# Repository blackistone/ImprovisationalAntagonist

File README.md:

# ImprovisationalAntagonist
Files from the development of the project merging hostile architectural approaches with machine learning strategies to produce systems that actively oppose performative predictability.
Current revision takes data via OSC from two AD8232 EMG sensonrs via and ESP32, processes that and sound data, and returns a trigger to pass TENS current from and external device when activity is deemed sufficiently predictable.

# Includes
Max files for ingestiona and interpretation of data and sending of shock triggers.  
ESP32 files written for arduino IDE to measure data from two sensors and send/receive OSC.  
KiCAD files for a board assembly allowing a third AD8232 muscle sensor, as well as relay for TENS voltage and indicator LED.

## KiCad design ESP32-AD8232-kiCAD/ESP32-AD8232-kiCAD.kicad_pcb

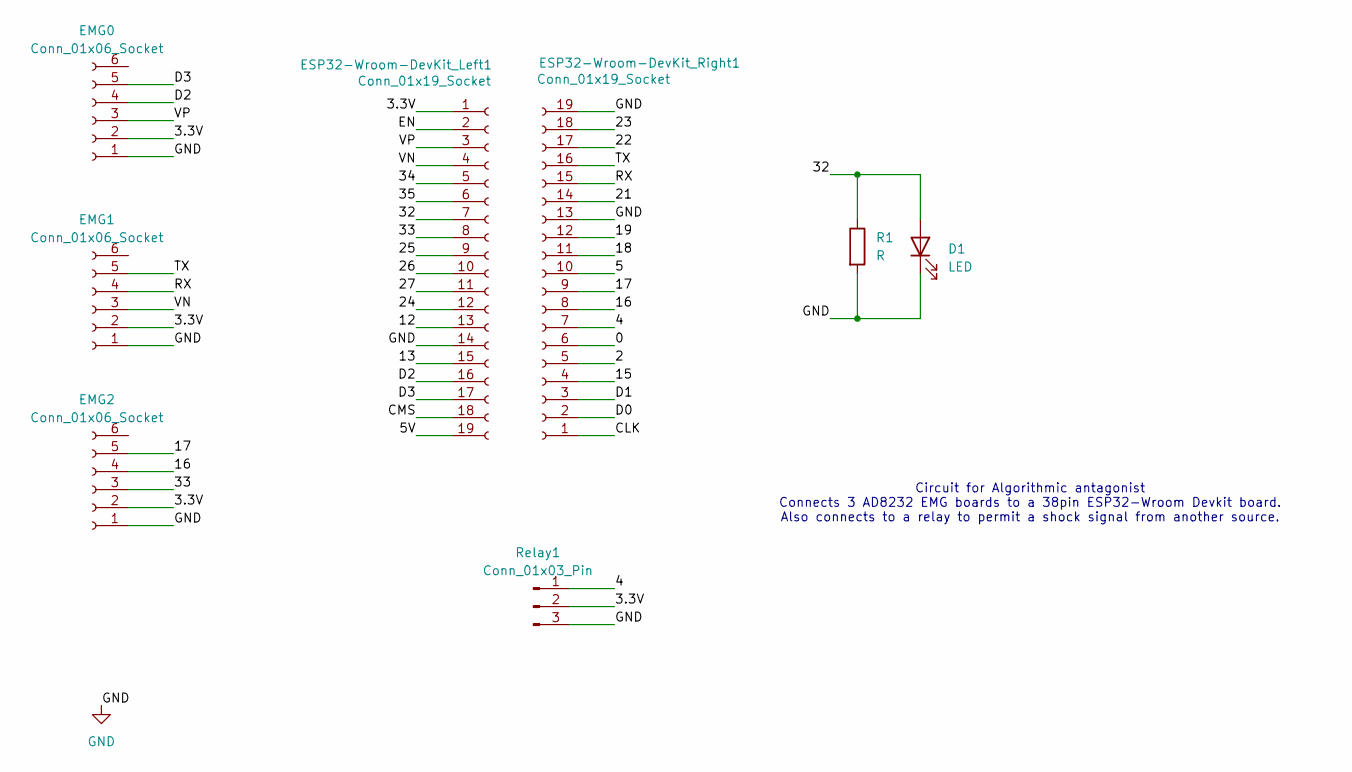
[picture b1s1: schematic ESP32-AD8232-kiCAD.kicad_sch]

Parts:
D1: LED; LED_D5.0mm
EMG0, EMG1, EMG2: Conn_01x06_Socket; PinSocket_1x06_P2.54mm_Vertical
ESP32-Wroom-DevKit_Left1, ESP32-Wroom-DevKit_Right1: Conn_01x19_Socket; PinSocket_1x19_P2.54mm_Vertical
R1: R; R_Axial_DIN0207_L6.3mm_D2.5mm_P15.24mm_Horizontal
Relay1: Conn_01x03_Pin; PinSocket_1x03_P2.54mm_Horizontal

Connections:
/0: ESP32-Wroom-DevKit_Right1.6
/2: ESP32-Wroom-DevKit_Right1.5
/3.3V: EMG0.2, EMG1.2, EMG2.2, ESP32-Wroom-DevKit_Left1.1, Relay1.2
/4: ESP32-Wroom-DevKit_Right1.7, Relay1.1
/5: ESP32-Wroom-DevKit_Right1.10
/5V: ESP32-Wroom-DevKit_Left1.19
/12: ESP32-Wroom-DevKit_Left1.13
/13: ESP32-Wroom-DevKit_Left1.15
/15: ESP32-Wroom-DevKit_Right1.4
/16: EMG2.4, ESP32-Wroom-DevKit_Right1.8
/17: EMG2.5, ESP32-Wroom-DevKit_Right1.9
/18: ESP32-Wroom-DevKit_Right1.11
/19: ESP32-Wroom-DevKit_Right1.12
/21: ESP32-Wroom-DevKit_Right1.14
/22: ESP32-Wroom-DevKit_Right1.17
/23: ESP32-Wroom-DevKit_Right1.18
/24: ESP32-Wroom-DevKit_Left1.12
/25: ESP32-Wroom-DevKit_Left1.9
/26: ESP32-Wroom-DevKit_Left1.10
/27: ESP32-Wroom-DevKit_Left1.11
/32: D1.2 (A), ESP32-Wroom-DevKit_Left1.7, R1.1
/33: EMG2.3, ESP32-Wroom-DevKit_Left1.8
/34: ESP32-Wroom-DevKit_Left1.5
/35: ESP32-Wroom-DevKit_Left1.6
/CLK: ESP32-Wroom-DevKit_Right1.1
/CMS: ESP32-Wroom-DevKit_Left1.18
/D0: ESP32-Wroom-DevKit_Right1.2
/D1: ESP32-Wroom-DevKit_Right1.3
/D2: EMG0.4, ESP32-Wroom-DevKit_Left1.16
/D3: EMG0.5, ESP32-Wroom-DevKit_Left1.17
/EN: ESP32-Wroom-DevKit_Left1.2
/RX: EMG1.4, ESP32-Wroom-DevKit_Right1.15
/TX: EMG1.5, ESP32-Wroom-DevKit_Right1.16
/VN: EMG1.3, ESP32-Wroom-DevKit_Left1.4
/VP: EMG0.3, ESP32-Wroom-DevKit_Left1.3
GND: D1.1 (K), EMG0.1, EMG1.1, EMG2.1, ESP32-Wroom-DevKit_Left1.14, ESP32-Wroom-DevKit_Right1.13, ESP32-Wroom-DevKit_Right1.19, R1.2, Relay1.3

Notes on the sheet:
Circuit for Algorithmic antagonist Connects 3 AD8232 EMG boards to a 38pin ESP32-Wroom Devkit board. Also connects to a relay to permit a shock signal from another source.

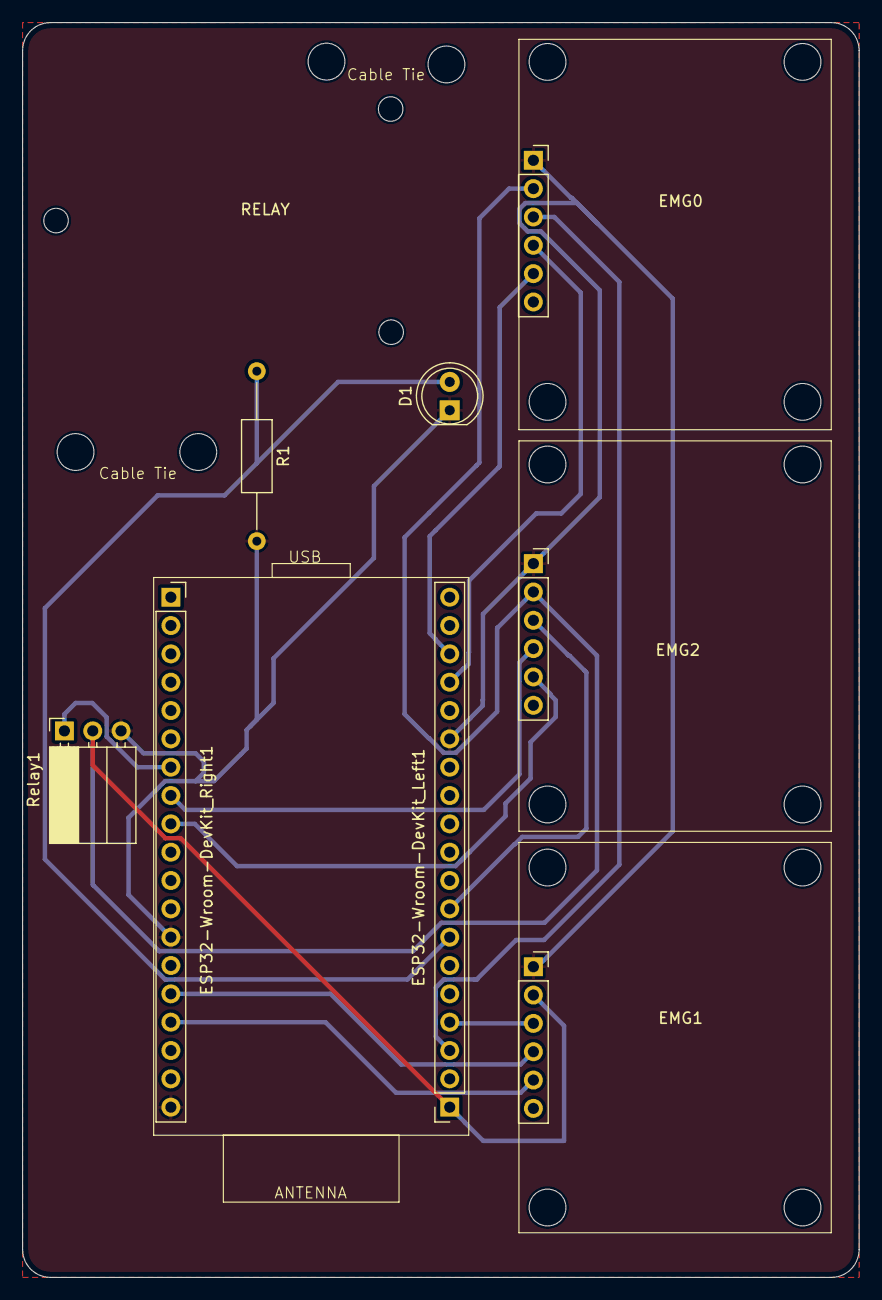
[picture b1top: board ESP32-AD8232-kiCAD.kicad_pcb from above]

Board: 2 copper layers, 75.0 x 112.5 mm, 9 parts (0 on the bottom side), 13 nets.

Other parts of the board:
RELAY: MountingHole_2.2mm_M2

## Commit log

2025-01-14 MaxMSP File
    Produced in MaxMSP 8, using packages FluCoMa and ML.Star
2025-01-14 Arduino firmware
2025-05-24 Add files via upload
    Latest updates, with improved filtering, analysis and visual design
